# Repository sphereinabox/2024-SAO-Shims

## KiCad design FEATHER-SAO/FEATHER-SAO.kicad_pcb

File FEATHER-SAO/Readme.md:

# Feather SAO

This SAO (SuperCon Add-On) was made to let me put an Adafruit feather board, like the Hallowing M0 or EdgeBadge or PyBadge handed out at previous supercon onto the badge as an SAO.

There's a swith at the bottom to connect the 3.3v pin to the feather to the 3.3v on on the SAO connector. Turn it off if you're connecting USB or your own battery, and turn it on to power your feather device from the badge's SAO connector.

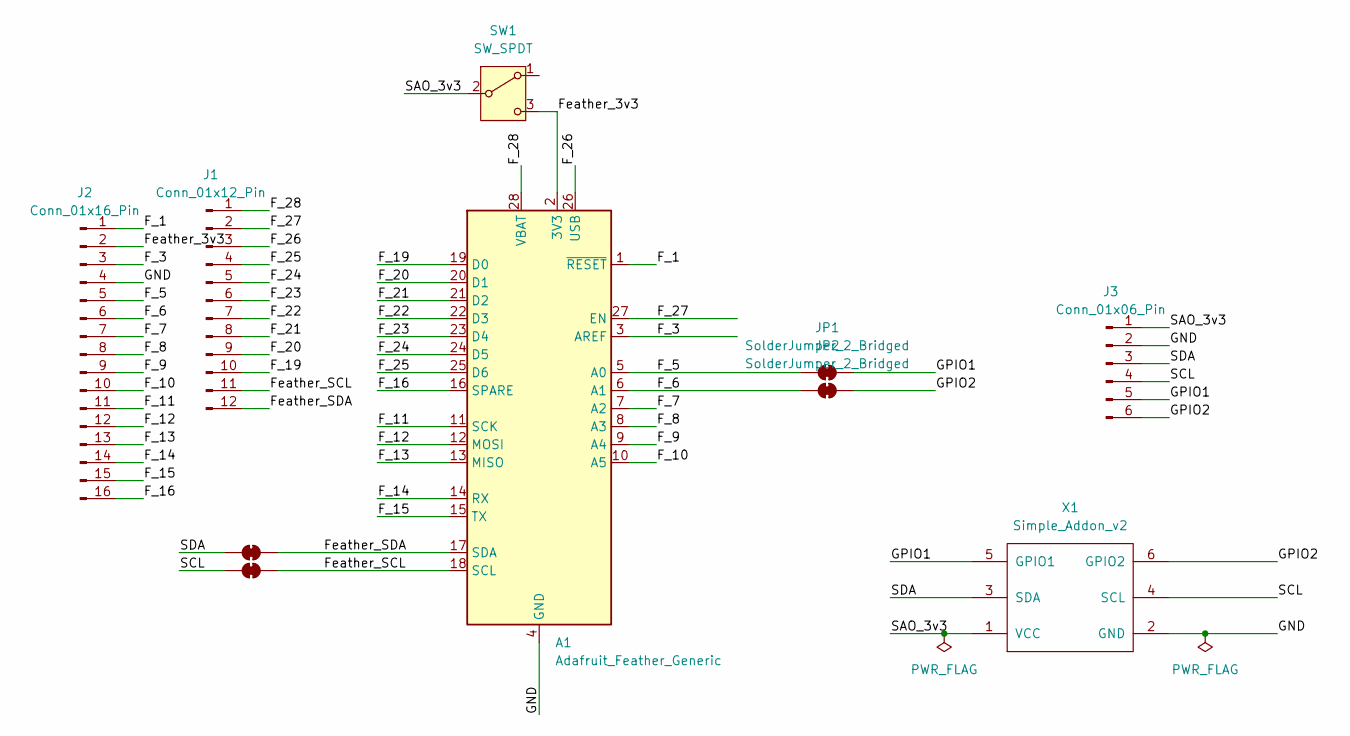
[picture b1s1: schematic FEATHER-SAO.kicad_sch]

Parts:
A1: Adafruit_Feather_Generic; Adafruit_Feather
J1: Conn_01x12_Pin; PinHeader_1x12_P2.54mm_Vertical
J2: Conn_01x16_Pin; PinHeader_1x16_P2.54mm_Vertical
J3: Conn_01x06_Pin; PinHeader_1x06_P2.54mm_Vertical
JP1, JP2, JP3, JP4: SolderJumper_2_Bridged; SolderJumper-2_P1.3mm_Bridged_RoundedPad1.0x1.5mm
SW1: SW_SPDT; SW_SPDT_PCM12
X1: Simple_Addon_v2; Simple_Addon_v2-SAO-2x3

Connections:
/F_1: A1.1 (~RESET), J2.1
/F_3: A1.3 (AREF), J2.3
/F_5: A1.5 (A0), J2.5, JP1.1 (A)
/F_6: A1.6 (A1), J2.6, JP2.1 (A)
/F_7: A1.7 (A2), J2.7
/F_8: A1.8 (A3), J2.8
/F_9: A1.9 (A4), J2.9
/F_10: A1.10 (A5), J2.10
/F_11: A1.11 (SCK), J2.11
/F_12: A1.12 (MOSI), J2.12
/F_13: A1.13 (MISO), J2.13
/F_14: A1.14 (RX), J2.14
/F_15: A1.15 (TX), J2.15
/F_16: A1.16 (SPARE), J2.16
/F_19: A1.19 (D0), J1.10
/F_20: A1.20 (D1), J1.9
/F_21: A1.21 (D2), J1.8
/F_22: A1.22 (D3), J1.7
/F_23: A1.23 (D4), J1.6
/F_24: A1.24 (D5), J1.5
/F_25: A1.25 (D6), J1.4
/F_26: A1.26 (USB), J1.3
/F_27: A1.27 (EN), J1.2
/F_28: A1.28 (VBAT), J1.1
/Feather_3v3: A1.2 (3V3), J2.2, SW1.3 (C)
/Feather_SCL: A1.18 (SCL), J1.11, JP4.2 (B)
/Feather_SDA: A1.17 (SDA), J1.12, JP3.2 (B)
/GND: A1.4 (GND), J2.4, J3.2, X1.2 (GND)
/GPIO1: J3.5, JP1.2 (B), X1.5 (GPIO1)
/GPIO2: J3.6, JP2.2 (B), X1.6 (GPIO2)
/SAO_3v3: J3.1, SW1.2 (B), X1.1 (VCC)
/SCL: J3.4, JP4.1 (A), X1.4 (SCL)
/SDA: J3.3, JP3.1 (A), X1.3 (SDA)

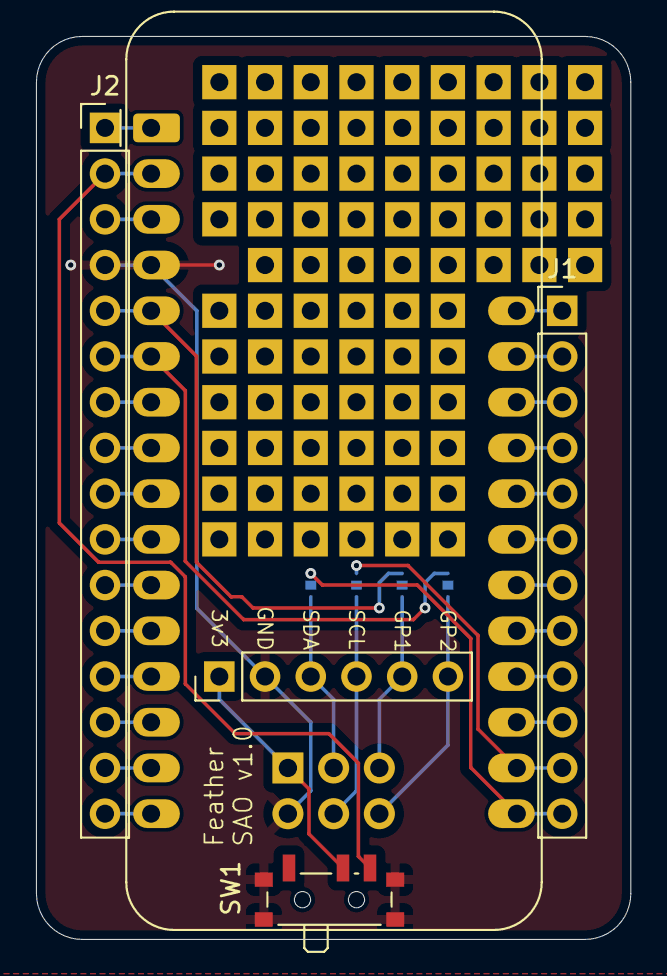
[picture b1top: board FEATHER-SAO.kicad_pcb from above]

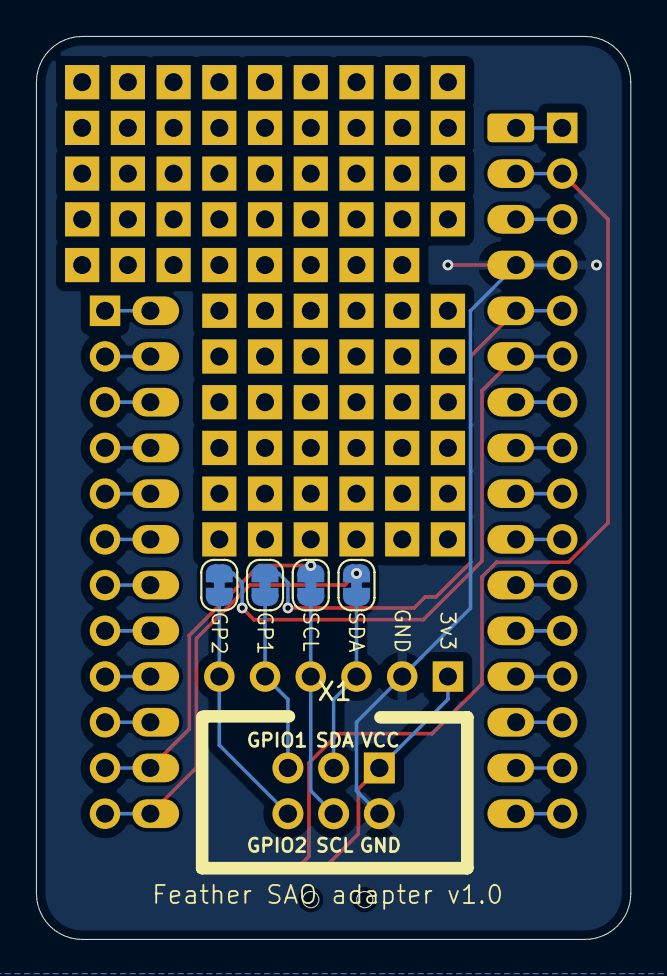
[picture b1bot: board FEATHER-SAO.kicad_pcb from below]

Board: 2 copper layers, 33.0 x 50.2 mm, 10 parts (4 on the bottom side), 33 nets.

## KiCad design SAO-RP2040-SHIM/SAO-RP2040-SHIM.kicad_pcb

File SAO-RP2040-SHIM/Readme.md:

# SAO-RP2040 Shim

This SAO (SuperCon Add-On) shim goes between your badge and your SAO to break out the SAO pins, and shuffle or disconnect them if needed

But it also connects an RP2040-Zero, to use with the pulseview from the open source sigrok project and the sigrok-rp2040 pi pico firmware see https://github.com/pico-coder/sigrok-pico/ and https://github.com/pico-coder/sigrok-pico/blob/main/AnalyzerDetails.md

I've connected the SAO pins to D2-D4 on the RP2040-zero. If you'd also like to connect them to the analog inputs use jumpers from the SAO pin breakouts to the analog input pin breakouts.

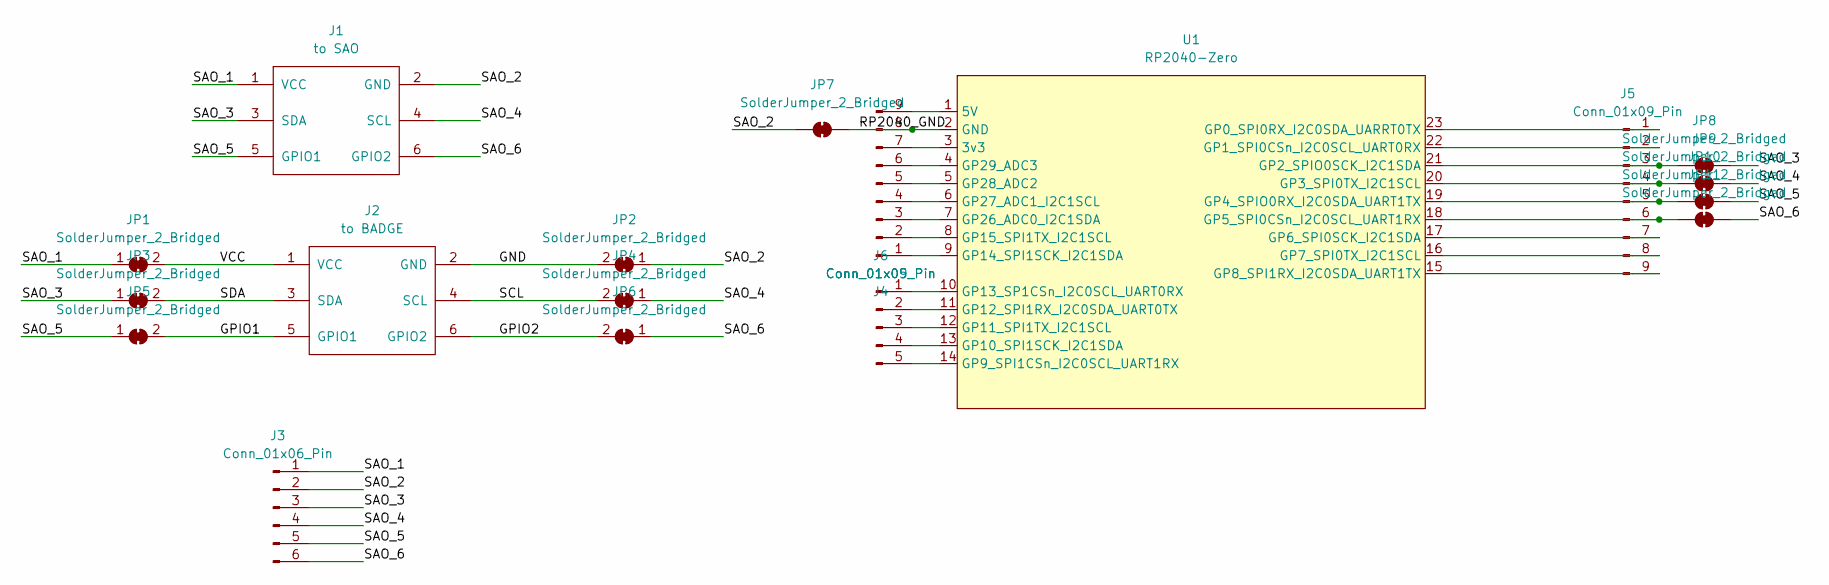
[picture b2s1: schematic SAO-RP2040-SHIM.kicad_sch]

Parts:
J1: to SAO; Simple_Addon_v2-BADGE-2x3
J2: to BADGE; Simple_Addon_v2-SAO-2x3
J3: Conn_01x06_Pin; PinHeader_1x06_P2.54mm_Horizontal
J4, J5: Conn_01x09_Pin; PinHeader_1x09_P2.54mm_Horizontal
J6: Conn_01x05_Pin; PinHeader_1x05_P2.54mm_Vertical
JP1, JP2, JP3, JP4, JP5, JP6: SolderJumper_2_Bridged; SolderJumper-2_Bridged_Pad_Holes
JP7, JP8, JP9, JP10, JP11: SolderJumper_2_Bridged; SolderJumper-2_P1.3mm_Bridged2Bar_RoundedPad1.0x1.5mm
U1: RP2040-Zero; RP2040-Zero-PinHeaders

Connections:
/GND: J2.2 (GND), JP2.2 (B)
/GPIO1: J2.5 (GPIO1), JP5.2 (B)
/GPIO2: J2.6 (GPIO2), JP6.2 (B)
/RP2040_GND: J4.8, JP7.2 (B), U1.2 (GND)
/SAO_1: J1.1 (VCC), J3.1, JP1.1 (A)
/SAO_2: J1.2 (GND), J3.2, JP2.1 (A), JP7.1 (A)
/SAO_3: J1.3 (SDA), J3.3, JP3.1 (A), JP8.2 (B)
/SAO_4: J1.4 (SCL), J3.4, JP4.1 (A), JP9.2 (B)
/SAO_5: J1.5 (GPIO1), J3.5, JP5.1 (A), JP10.2 (B)
/SAO_6: J1.6 (GPIO2), J3.6, JP6.1 (A), JP11.2 (B)
/SCL: J2.4 (SCL), JP4.2 (B)
/SDA: J2.3 (SDA), JP3.2 (B)
/VCC: J2.1 (VCC), JP1.2 (B)
unnamed: J4.1, U1.9 (GP14_SPI1SCK_I2C1SDA)
unnamed: J4.2, U1.8 (GP15_SPI1TX_I2C1SCL)
unnamed: J4.3, U1.7 (GP26_ADC0_I2C1SDA)
unnamed: J4.4, U1.6 (GP27_ADC1_I2C1SCL)
unnamed: J4.5, U1.5 (GP28_ADC2)
unnamed: J4.6, U1.4 (GP29_ADC3)
unnamed: J4.7, U1.3 (3v3)
unnamed: J4.9, U1.1 (5V)
unnamed: J5.1, U1.23 (GP0_SPI0RX_I2C0SDA_UARRT0TX)
unnamed: J5.2, U1.22 (GP1_SPI0CSn_I2C0SCL_UART0RX)
unnamed: J5.3, JP8.1 (A), U1.21 (GP2_SPIO0SCK_I2C1SDA)
unnamed: J5.4, JP9.1 (A), U1.20 (GP3_SPI0TX_I2C1SCL)
unnamed: J5.5, JP10.1 (A), U1.19 (GP4_SPIO0RX_I2C0SDA_UART1TX)
unnamed: J5.6, JP11.1 (A), U1.18 (GP5_SPI0CSn_I2C0SCL_UART1RX)
unnamed: J5.7, U1.17 (GP6_SPI0SCK_I2C1SDA)
unnamed: J5.8, U1.16 (GP7_SPI0TX_I2C1SCL)
unnamed: J5.9, U1.15 (GP8_SPI1RX_I2C0SDA_UART1TX)
unnamed: J6.1, U1.10 (GP13_SP1CSn_I2C0SCL_UART0RX)
unnamed: J6.2, U1.11 (GP12_SPI1RX_I2C0SDA_UART0TX)
unnamed: J6.3, U1.12 (GP11_SPI1TX_I2C1SCL)
unnamed: J6.4, U1.13 (GP10_SPI1SCK_I2C1SDA)
unnamed: J6.5, U1.14 (GP9_SPI1CSn_I2C0SCL_UART1RX)

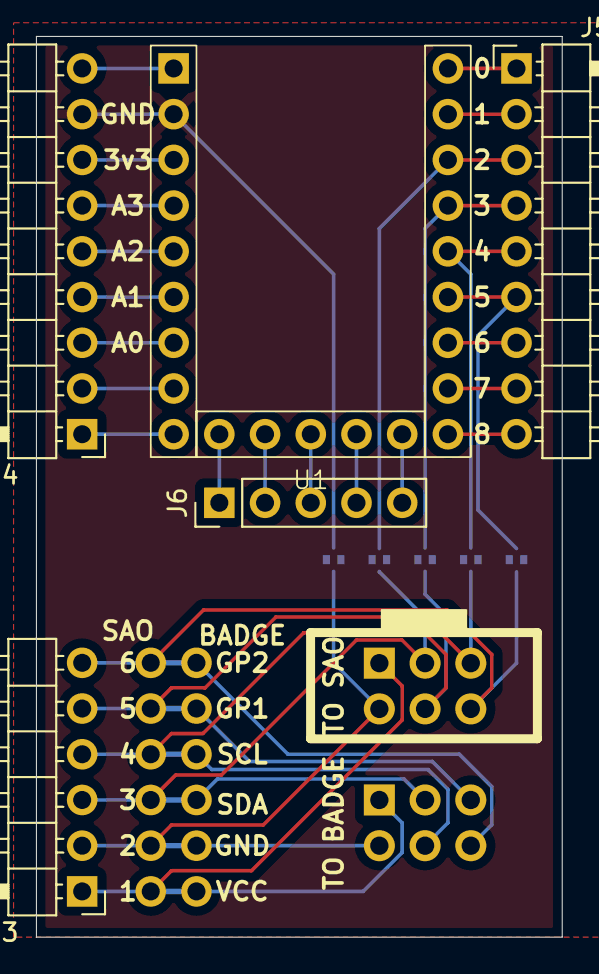
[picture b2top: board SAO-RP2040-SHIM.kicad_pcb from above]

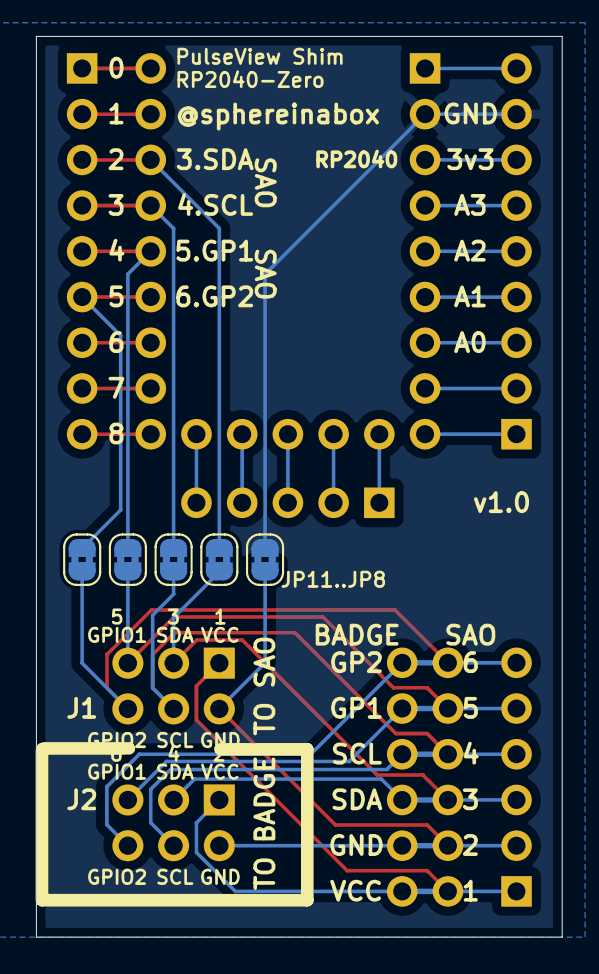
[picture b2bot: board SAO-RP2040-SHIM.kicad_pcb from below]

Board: 2 copper layers, 29.2 x 50.0 mm, 18 parts (11 on the bottom side), 35 nets.

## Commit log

2024-10-17 Add images to readme
2024-10-20 Add more boards
2024-10-20 kikit exports and changes to pass DRC
2024-10-21 Update readme files
